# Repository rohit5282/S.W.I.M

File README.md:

# S.W.I.M (SEQUENTIAL WAVE IMPRINTING MACHINES )
The SWIM device is a novel integration of audio signal processing, LED visualization, and mechanical motion control. By capturing audio data and mapping it to light intensity on an RGB LED strip, the machine aims to translate sound into a dynamic and visually engaging format. This project builds on the principle of audio waveform visualization, bringing it into a three-dimensional space through a combination of light and motion.

The S.W.I.M (Sequential Wave Imprinting Machines) project integrates several key hardware components to capture, process, and display audio signals in a dynamic, multi-sensory format. At the input stage, a mic/preamp board captures environmental audio, boosting the signal for processing, while a 3.5mm plug to RCA cable provides an alternative for capturing stereo audio from external sources. The central processing unit, a Raspberry Pi RP2040-Zero board, acts as the project's brain, handling real-time audio signal processing, controlling the RGB LED strip, and managing the stepper motor for motion control. The high-density RGB LED strip, featuring 144 LEDs per meter, serves as the primary visual output, mapping waveform amplitude to color and brightness, enabling high-fidelity visualization of sound. Additionally, a stepper motor, powered by a driver board, adds motion control, rotating or moving surfaces to create a spatial representation of the waveform, enhancing the visual experience by presenting sound waves across both time and space.

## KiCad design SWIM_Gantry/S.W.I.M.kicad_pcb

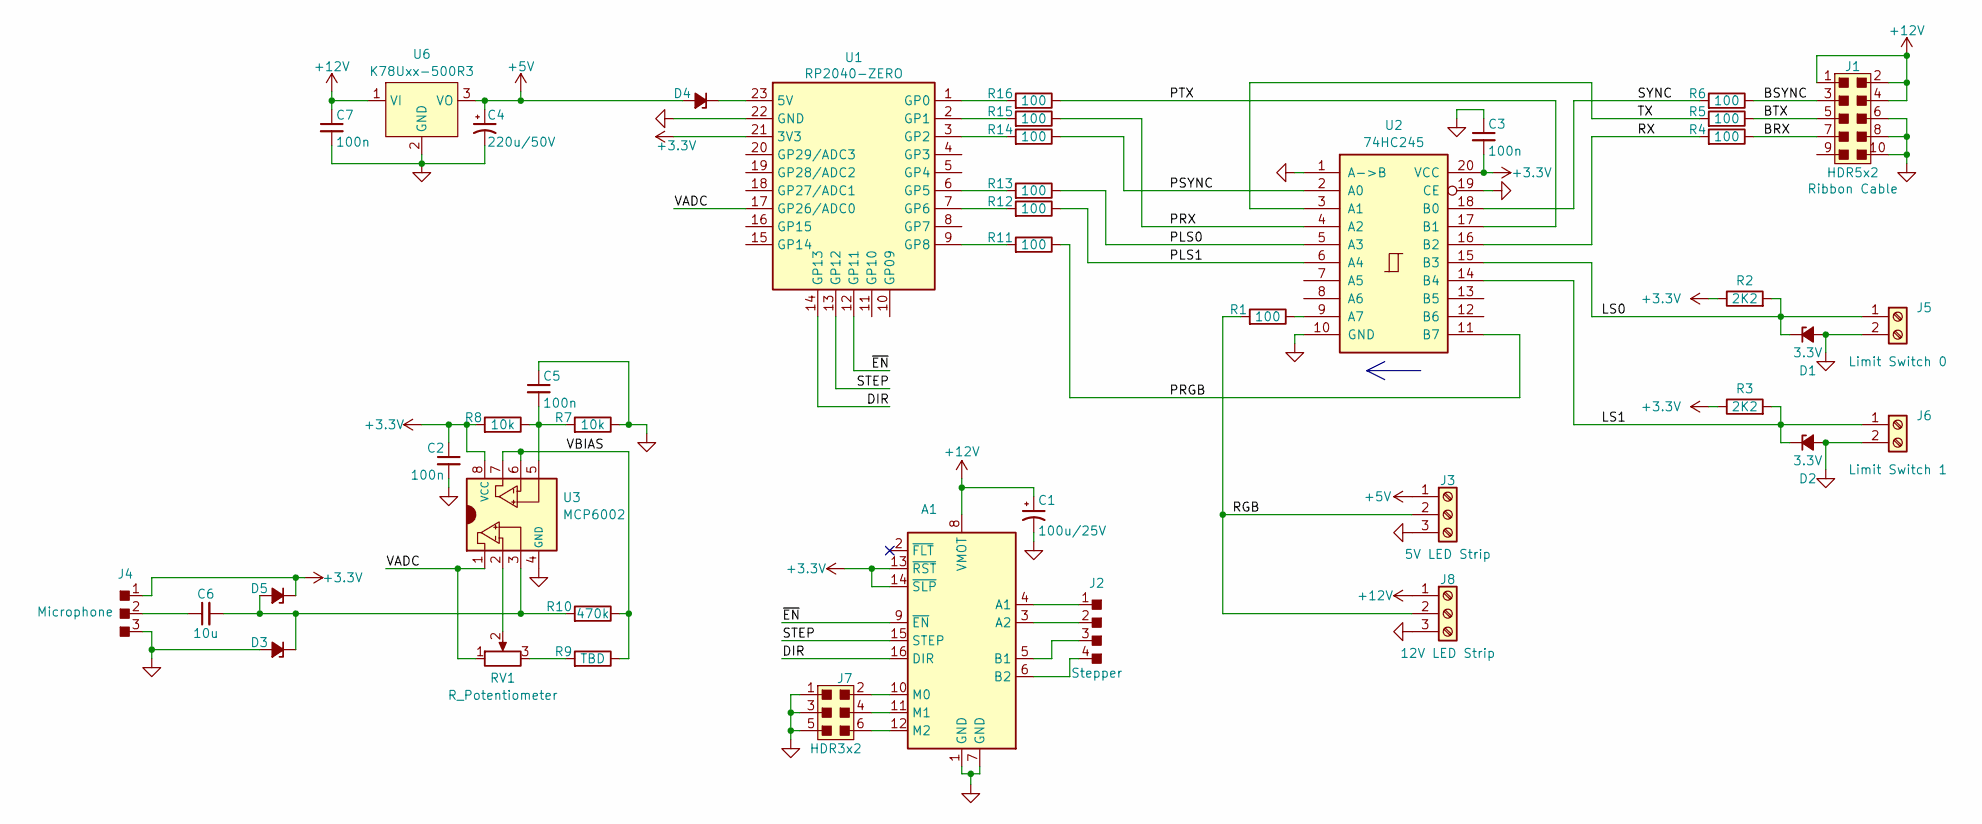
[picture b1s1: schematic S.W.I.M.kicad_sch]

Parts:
A1: Pololu_Breakout_DRV8825; Pololu_Breakout-16_15.2x20.3mm
C1: 100u/25V; CP_Radial_D10.0mm_P2.50mm_P5.00mm
C2, C3, C5, C7: 100n; C_Ceramic-100mil-THT
C4: 220u/50V; CP_Radial_D10.0mm_P2.50mm_P5.00mm
C6: 10u; C_Ceramic-100mil-THT
D1, D2: 3.3V; D_A-405_P7.62mm_Horizontal
D3, D4, D5: 30V; D_A-405_P7.62mm_Horizontal
J1: HDR5x2; Pin_Header_Straight_2x05_Pitch2.54mm
J2: HDR4; SW_DIP_SPSTx02_Slide_6.7x6.64mm_W7.62mm_P2.54mm_LowProfile
J3, J8: Screw_Terminal_01x03; TerminalBlock_4Ucon_1x03_P3.50mm_Vertical
J4: HDR3; Pin_Header_Straight_1x03_Pitch2.54mm
J5, J6: Screw_Terminal_01x02; TerminalBlock_4Ucon_1x02_P3.50mm_Vertical
J7: HDR3x2; Pin_Header_Straight_2x03_Pitch2.54mm
R1, R4, R5, R6, R11, R12, R13, R14, R15, R16: 100; R_Axial_DIN0207_L6.3mm_D2.5mm_P7.62mm_Horizontal
R2, R3: 2K2; R_Axial_DIN0207_L6.3mm_D2.5mm_P7.62mm_Horizontal
R7, R8: 10k; R_Axial_DIN0207_L6.3mm_D2.5mm_P7.62mm_Horizontal
R9: TBD; R_Axial_DIN0207_L6.3mm_D2.5mm_P7.62mm_Horizontal
R10: 470k; R_Axial_DIN0207_L6.3mm_D2.5mm_P7.62mm_Horizontal
RV1: R_Potentiometer; Potentiometer_Runtron_RM-065_Vertical
U1: RP2040-ZERO; MODULE_RP2040-ZERO; PARTREV NA
U2: 74HC245; DIP-20_W7.62mm_Socket_LongPads
U3: MCP6002; DIP-8_W7.62mm_Socket_LongPads
U6: K78Uxx-500R3; TSR0P5_TRP

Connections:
+3.3V: A1.13 (~RST), A1.14 (~SLP), C2.1, C3.2, D5.1 (K), J4.1, R2.1, R3.1, R8.2, U1.21 (3V3), U2.20 (VCC), U3.8 (VCC)
+5V: C4.1, D4.2 (A), J3.1, U6.3 (VO)
+12V: A1.8 (VMOT), C1.1, C7.1, J1.1, J1.2, J1.4, J8.1, U6.1 (VI)
/BRX: J1.7, R4.1
/BSYNC: J1.3, R6.1
/BTX: J1.5, R5.1
/DIR: A1.16 (DIR), U1.14 (GP13)
/LS0: D1.1 (K), J5.1, R2.2, U2.15 (B3)
/LS1: D2.1 (K), J6.1, R3.2, U2.14 (B4)
/PLS0: R13.1, U2.5 (A3)
/PLS1: R12.1, U2.6 (A4)
/PRGB: R11.1, U2.11 (B7)
/PRX: R15.1, U2.4 (A2)
/PSYNC: R14.1, U2.2 (A0)
/PTX: R16.1, U2.17 (B1)
/RGB: J3.2, J8.2, R1.2
/RX: R4.2, U2.16 (B2)
/STEP: A1.15 (STEP), U1.13 (GP12)
/SYNC: R6.2, U2.18 (B0)
/TX: R5.2, U2.3 (A1)
/VADC: RV1.1, U1.17 (GP26/ADC0), U3.1 (AO)
/VBIAS: R9.1, R10.1, U3.6 (B-), U3.7 (BO)
/~EN: A1.9 (~EN), U1.12 (GP11)
GND: A1.1 (GND), A1.7 (GND), C1.2, C2.2, C3.1, C4.2, C5.1, C7.2, D1.2 (A), D2.2 (A), D3.2 (A), J1.6, J1.8, J1.10, J3.3, J4.3, J5.2, J6.2, J7.1, J7.3, J7.5, J8.3, R7.1, U1.22 (GND), U2.1 (A->B), U2.10 (GND), U2.19 (CE), U3.4 (GND), U6.2 (GND)
unnamed: A1.4 (A1), J2.1
unnamed: A1.3 (A2), J2.2
unnamed: A1.5 (B1), J2.3
unnamed: A1.6 (B2), J2.4
unnamed: A1.10 (M0), J7.2
unnamed: A1.11 (M1), J7.4
unnamed: A1.12 (M2), J7.6
unnamed: C6.1, J4.2
unnamed: C6.2, D3.1 (K), D5.2 (A), R10.2, U3.3 (A+)
unnamed: D4.1 (K), U1.23 (5V)
unnamed: R9.2, RV1.3
unnamed: R16.2, U1.1 (GP0)
unnamed: R15.2, U1.2 (GP1)
unnamed: R14.2, U1.3 (GP2)
unnamed: R13.2, U1.6 (GP5)
unnamed: R12.2, U1.7 (GP6)
unnamed: R11.2, U1.9 (GP8)
unnamed: R1.1, U2.9 (A7)
unnamed: RV1.2, U3.2 (A-)
unnamed: C5.2, R7.2, R8.1, U3.5 (B+)

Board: 2 copper layers, 42 parts (0 on the bottom side), 44 nets, no tracks yet.

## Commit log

2024-09-29 Add files via upload
    Assignment 1
